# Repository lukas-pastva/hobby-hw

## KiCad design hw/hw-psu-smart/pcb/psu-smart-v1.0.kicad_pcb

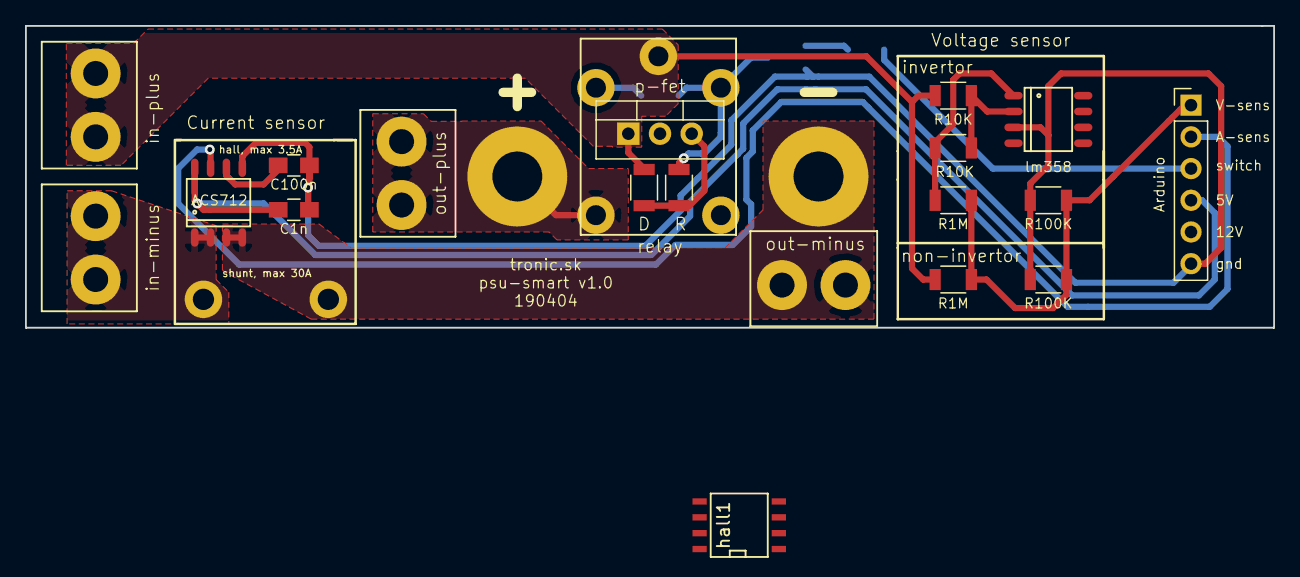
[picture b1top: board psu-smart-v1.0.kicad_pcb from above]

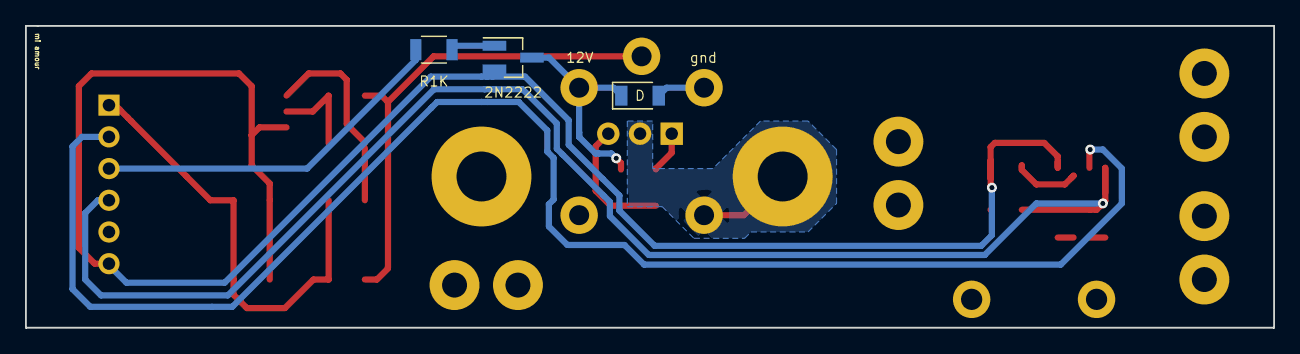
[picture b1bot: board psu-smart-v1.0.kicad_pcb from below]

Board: 2 copper layers, 100.0 x 24.2 mm, 26 parts (3 on the bottom side), 16 nets.

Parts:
ACS712: ACS712; SO-8
C1, C2: C; C_0805_HandSoldering
D1: D; D_1206
D2: D; R_1206
J1: mosfet; TO-220-3_Vertical
J2: shunt; psw-shunt
Q1: Q_PNP_BCE; SOT-23_Handsoldering
R1, R2, R3, R4, R5, R6, R7, R8: R; R_1206
arduino1: arduino; Pin_Header_Straight_1x06_Pitch2.54mm
hall1: hall1; SOIC-8-N
in-minus1: in-minus; psw-konektor-zeleny
in-plus1: in-plus; psw-konektor-zeleny
invertor1: invertor; SO-8
out1: out; psw-bananik
out-gnd1: out-gnd; psw-bananik
out-minus1: out-minus; psw-konektor-zeleny
out-plus1: out-plus; psw-konektor-zeleny
relay1: relay1; psw-relay-small

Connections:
12V: J1.1, R1.2, R2.2, R8.1, in-plus1.1, in-plus1.2, relay1.3
12V-out: J1.2, out1.1, out-plus1.1, out-plus1.2, relay1.5
unnamed: ACS712.6, C2.2
unnamed: D1.1, D2.2, Q1.3, relay1.1
unnamed: D1.2, relay1.2
unnamed: D2.1, J1.3, R8.2
unnamed: Q1.1, R7.2
unnamed: R1.1, R3.2, invertor1.2
unnamed: R3.1, R6.1, invertor1.1
a-sens: ACS712.7, arduino1.2
arduino-5V: ACS712.8, C1.2, arduino1.4
arduino-gnd: ACS712.5, C1.1, C2.1, Q1.2, R4.1, R5.2, arduino1.6, invertor1.3
arduino-relay: R7.1, arduino1.3
in-gnd: ACS712.1, ACS712.2, J2.1, in-minus1.1, in-minus1.2
out-gnd: ACS712.3, ACS712.4, J2.2, out-gnd1.1, out-minus1.1, out-minus1.2
v-sens: R2.1, R4.2, R5.1, R6.2, arduino1.1

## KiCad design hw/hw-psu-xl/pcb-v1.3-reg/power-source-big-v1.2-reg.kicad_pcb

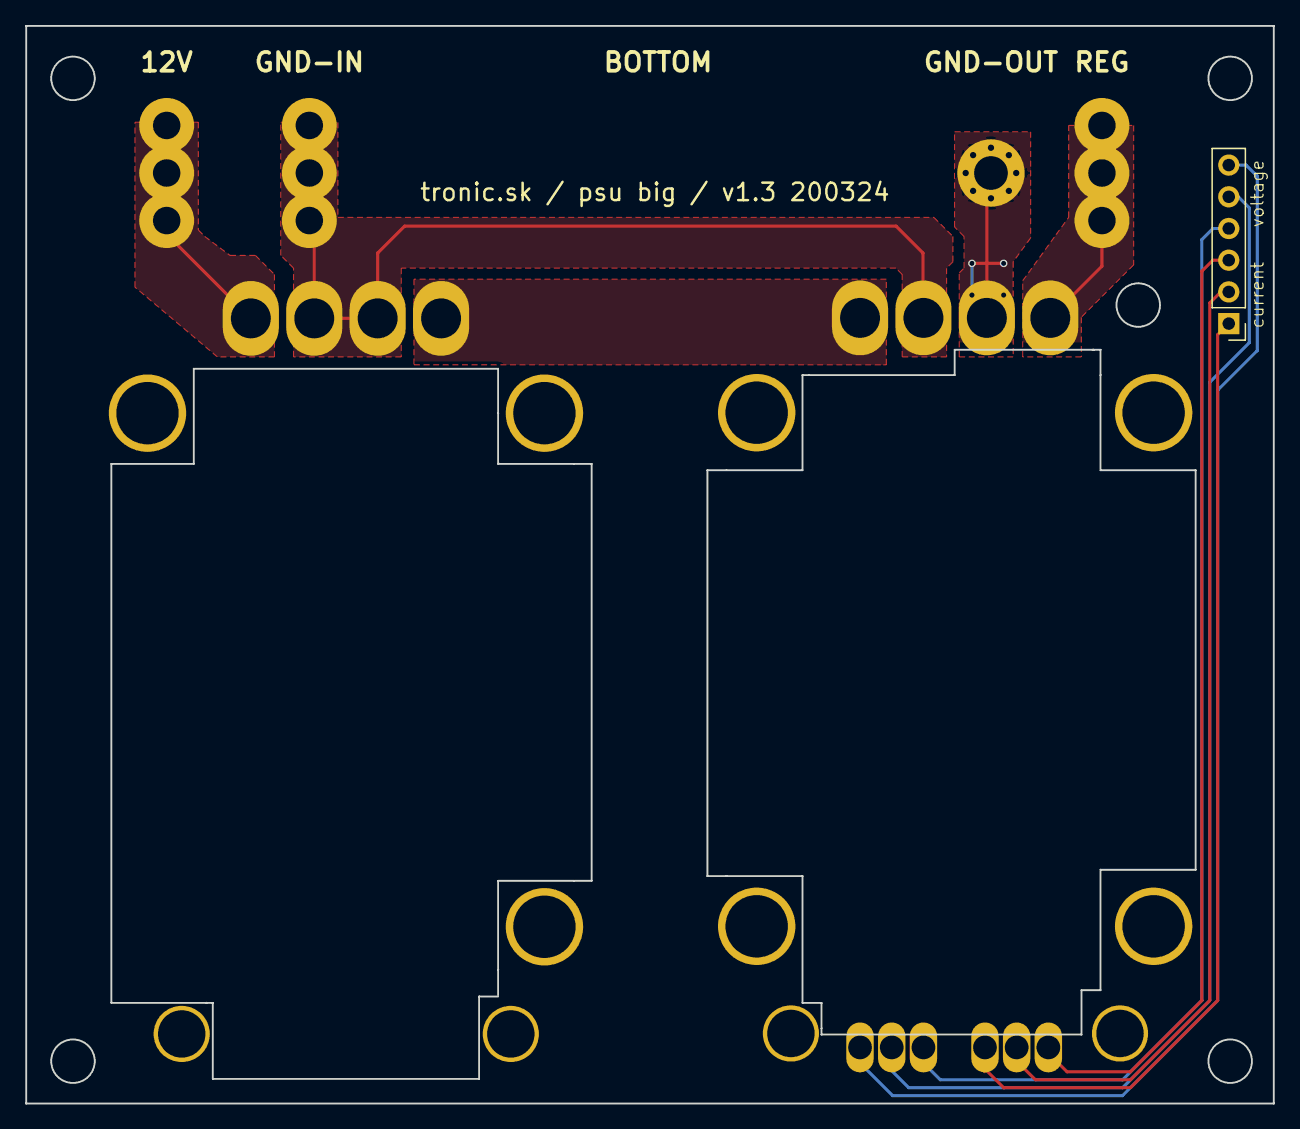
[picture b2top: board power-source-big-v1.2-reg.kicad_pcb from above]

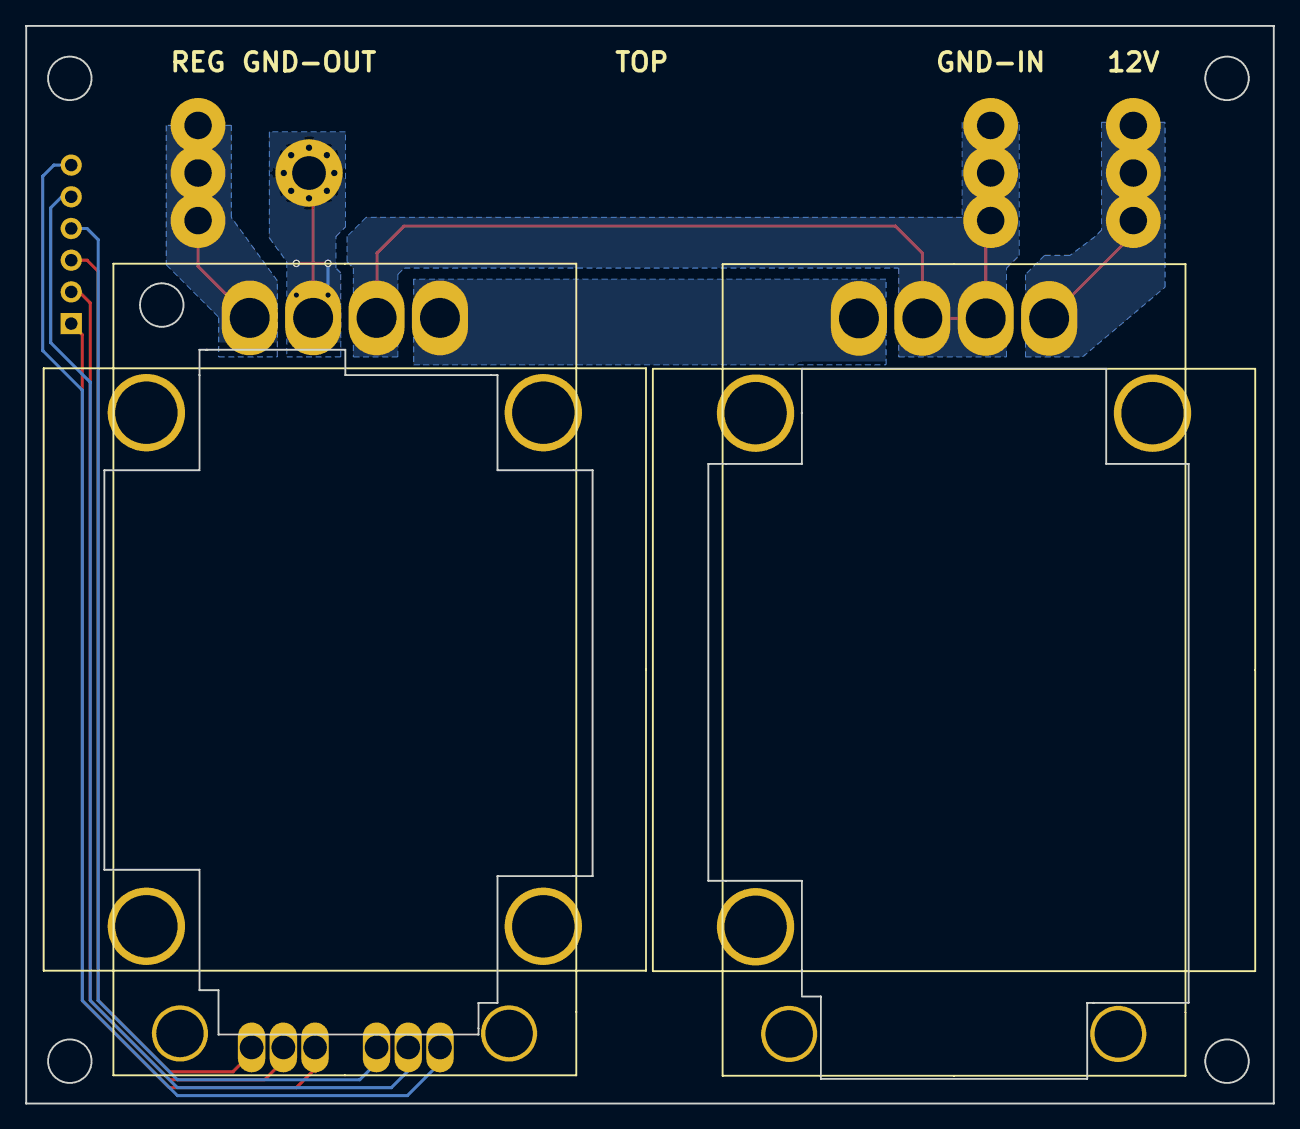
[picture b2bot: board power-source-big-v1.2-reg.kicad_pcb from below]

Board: 2 copper layers, 100.0 x 86.3 mm, 13 parts (2 on the bottom side), 11 nets.

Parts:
12V1, 12V2, 12V3, 12V10, 12V11, 12V12: 12V; MountingHole_2.2mm_M2_Pad
boost1: boost; psw-reg-big-boost
buck1: buck; psw-reg-big-buck
conn-reg-v-a1: conn-reg-v-a; Pin_Header_Straight_1x06_Pitch2.54mm
gnd1, gnd2, gnd3: gnd; MountingHole_2.2mm_M2_Pad
gnd-reg1: gnd-reg; MountingHole_2.7mm_Pad_Via

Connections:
12V: 12V1.1, 12V2.1, 12V3.1, boost1.4
12V-reg: 12V10.1, 12V11.1, 12V12.1, buck1.1
unnamed: boost1.1, buck1.4
gnd: boost1.2, boost1.3, buck1.3, gnd1.1, gnd2.1, gnd3.1
gnd-reg: buck1.2, gnd-reg1.1
reg-a-1: buck1.8, conn-reg-v-a1.4
reg-a-2: buck1.9, conn-reg-v-a1.5
reg-a-3: buck1.10, conn-reg-v-a1.6
reg-v-1: buck1.7, conn-reg-v-a1.1
reg-v-2: buck1.6, conn-reg-v-a1.2
reg-v-3: buck1.5, conn-reg-v-a1.3

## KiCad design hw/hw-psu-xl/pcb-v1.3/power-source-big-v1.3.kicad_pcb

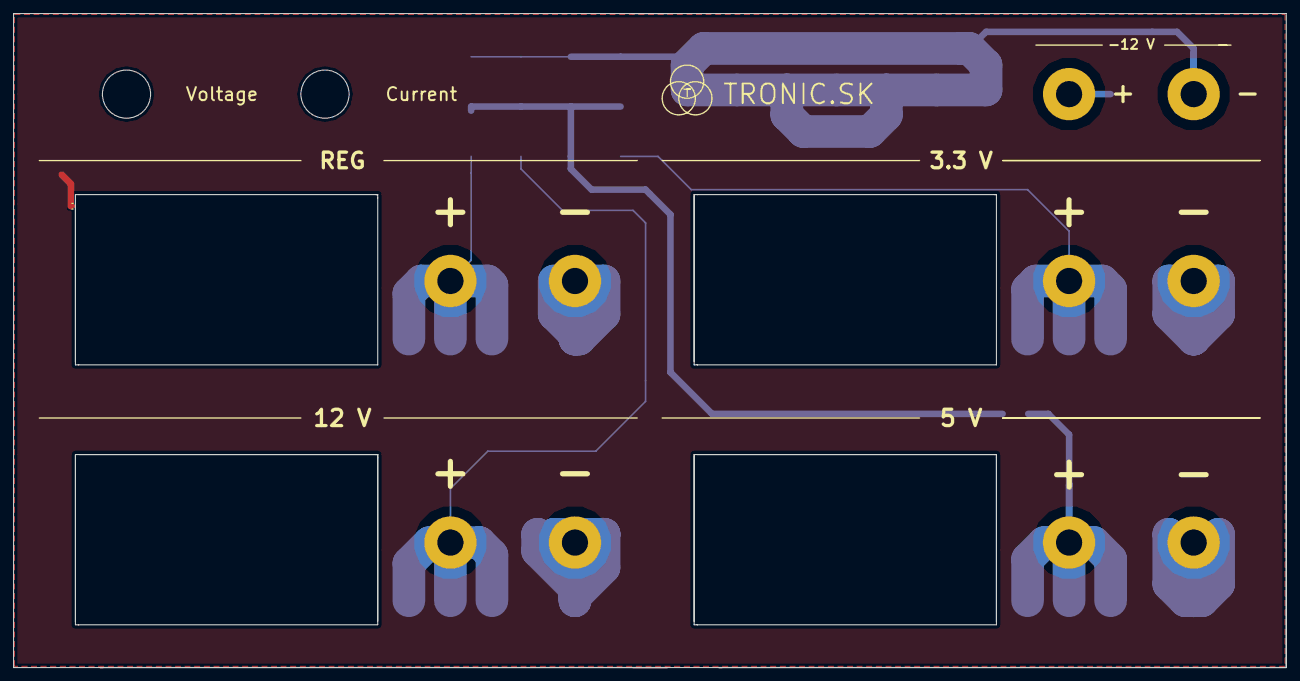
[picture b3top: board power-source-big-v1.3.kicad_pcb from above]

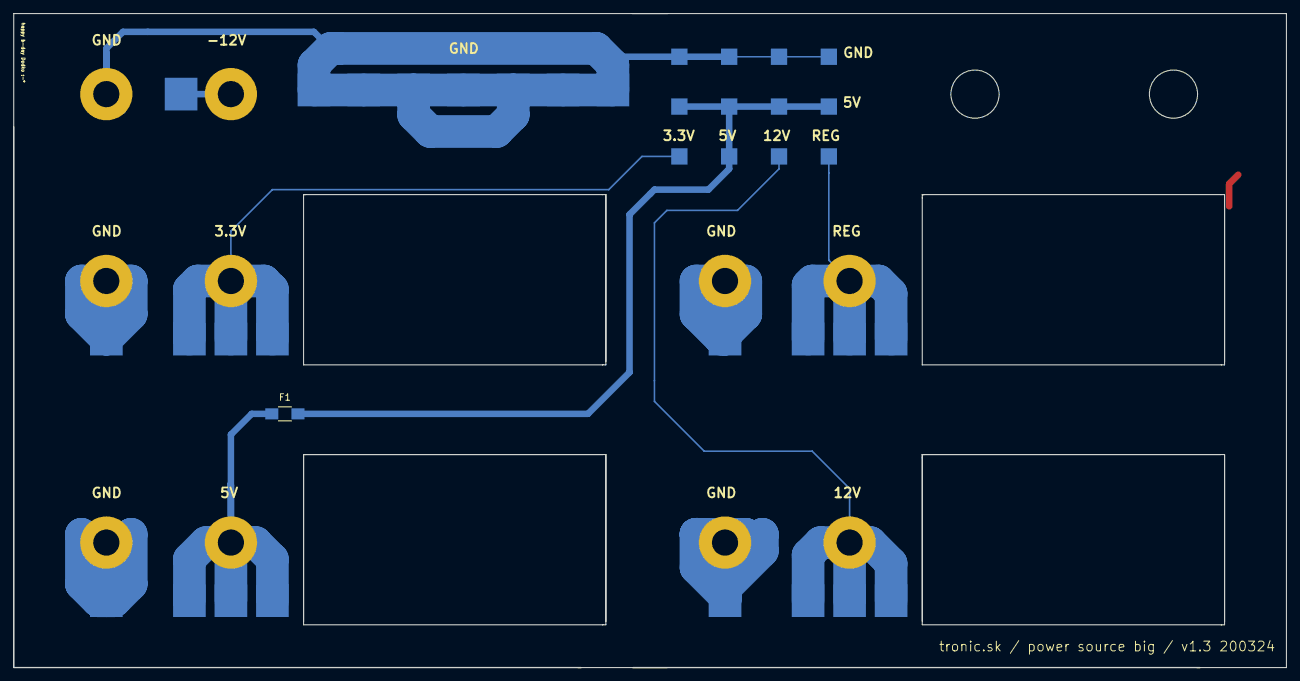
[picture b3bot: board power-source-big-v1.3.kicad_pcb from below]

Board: 2 copper layers, 194.6 x 100.0 mm, 48 parts (47 on the bottom side), 11 nets.

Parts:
3V1, 3V2, 3V3: 3V; psw-kontakt-smd-velky
3V-measure1: 3V-measure; psw-kontakt-smd-maly
5V1, 5V2, 5V3: 5V; psw-kontakt-smd-velky
5V-measure1: 5V-measure; psw-kontakt-smd-maly
5V-meter1, 5V-meter2, 5V-meter3, 5V-meter4: 5V-meter; psw-kontakt-smd-maly
12V1, 12V2, 12V3: 12V; psw-kontakt-smd-velky
12V-measure1: 12V-measure; psw-kontakt-smd-maly
-12V1: -12V; psw-bananik
-12V2: -12V; psw-kontakt-smd-velky
F1: Fuse; R_1206_HandSoldering
GND-3V1, GND-5V1: GND-3V; psw-bananik
GND-3V2: GND-3V; psw-kontakt-smd-velky
GND-5V2: GND-5V; psw-kontakt-smd-velky
GND-12V1, GND-12V3: GND-12V; psw-bananik
GND-12V2: GND-12V; psw-kontakt-smd-velky
GND-REG1: GND-REG; psw-bananik
GND-REG2: GND-REG; psw-kontakt-smd-velky
R1: R; R_0201
REG1, REG2, REG3: REG; psw-kontakt-smd-velky
REG-measure1: REG-measure; psw-kontakt-smd-maly
gnd1, gnd2, gnd3, gnd4, gnd5, gnd6, gnd7: gnd; psw-kontakt-smd-velky
gnd-meter1, gnd-meter2, gnd-meter3, gnd-meter4: gnd-meter; psw-kontakt-smd-maly
panel-3V1: panel-3V; psw-bananik
panel-5V1: panel-5V; psw-bananik
panel-12V1: panel-12V; psw-bananik
panel-REG1: panel-REG; psw-bananik

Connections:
3V: 3V1.1, 3V2.1, 3V3.1, 3V-measure1.1, panel-3V1.1
5V: 5V1.1, 5V2.1, 5V3.1, 5V-measure1.1, 5V-meter1.1, 5V-meter2.1, 5V-meter3.1, 5V-meter4.1, F1.1, F1.2, panel-5V1.1
12V: 12V1.1, 12V2.1, 12V3.1, 12V-measure1.1, panel-12V1.1
-12V: -12V1.1, -12V2.1
GND: GND-12V3.1, gnd1.1, gnd2.1, gnd3.1, gnd4.1, gnd5.1, gnd6.1, gnd7.1, gnd-meter1.1, gnd-meter2.1, gnd-meter3.1, gnd-meter4.1
GND-3V: GND-3V1.1, GND-3V2.1
GND-5V: GND-5V1.1, GND-5V2.1
GND-12V: GND-12V1.1, GND-12V2.1
GND-REG: GND-REG1.1, GND-REG2.1
REG: REG1.1, REG2.1, REG3.1, REG-measure1.1, panel-REG1.1
aaa: R1.1, R1.2

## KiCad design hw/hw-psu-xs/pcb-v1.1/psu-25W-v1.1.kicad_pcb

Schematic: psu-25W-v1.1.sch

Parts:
12V1: 12V; MountingHole_2.5mm_Pad_Via
GND1: GND; MountingHole_2.5mm_Pad_Via
J1: USB_A; psw-usb-a-vertical
J3: zem; psw-kontakt-smd-velky
J9, J10: pot-1; psw-pot-through-horizontal
J12, J13, J14, J15: srobik; psw-srobik-3.5mm
R1, R2, R3, R4: R; R_1206
fan1: fan; Pin_Header_Straight_1x03_Pitch2.54mm
minus1: minus; psw-bananik
plus1: plus; psw-bananik
reg1: reg; psw-reg-small-buck-boost
reg-usb1: reg-usb; psw-dc-dc-lm2596-HOLE
va1: va; psw-va-meter

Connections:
5V: J1.4 (GND), R4.2, reg-usb1.3
12V: 12V1.1, R3.2, reg1.4, reg-usb1.1, va1.1
12v-reg: plus1.1, reg1.1, va1.3
unnamed: R3.1, R4.1, fan1.1, fan1.2
gnd: GND1.1, J1.1 (VBUS), J1.5 (Shield), fan1.3, reg1.2, reg1.3, reg-usb1.2, reg-usb1.4, va1.2, va1.4
gnd-out: va1.5; also elsewhere on the board
reg-i-1: J10.3, R2.2, reg1.5
reg-i-2: J10.2, reg1.6
reg-i-3: J10.1, R2.1, reg1.7
reg-u-1: J9.3, R1.1, reg1.8
reg-u-2: J9.2, reg1.9
reg-u-3: J9.1, R1.2, reg1.10
zem: J3.1, J12.1, J13.1, J14.1, J15.1

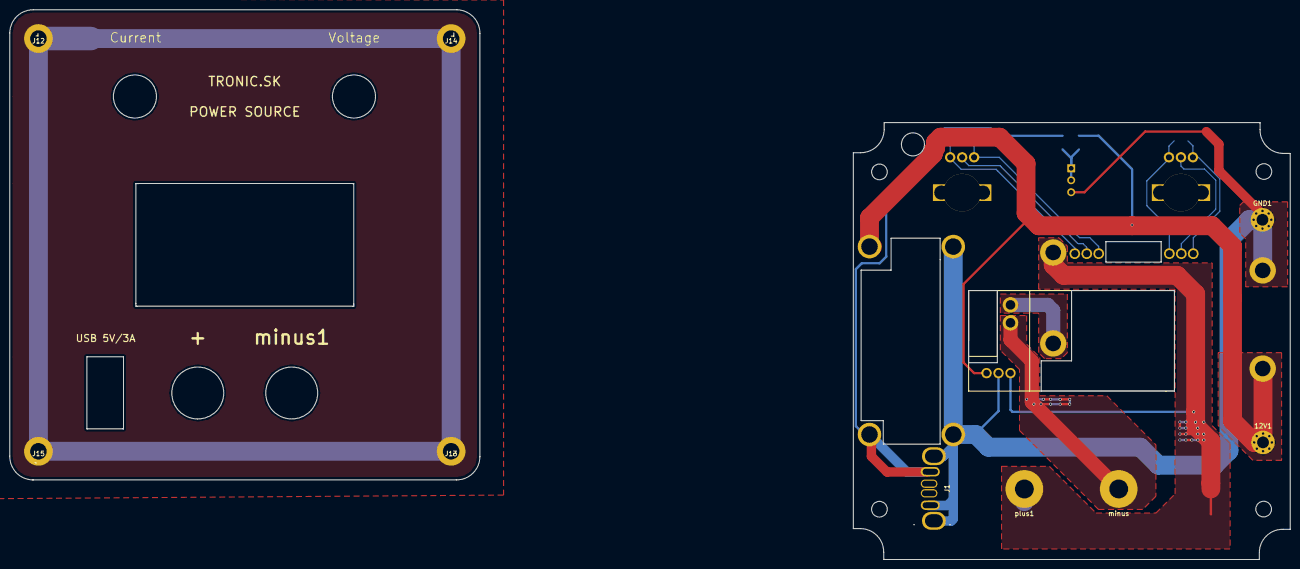
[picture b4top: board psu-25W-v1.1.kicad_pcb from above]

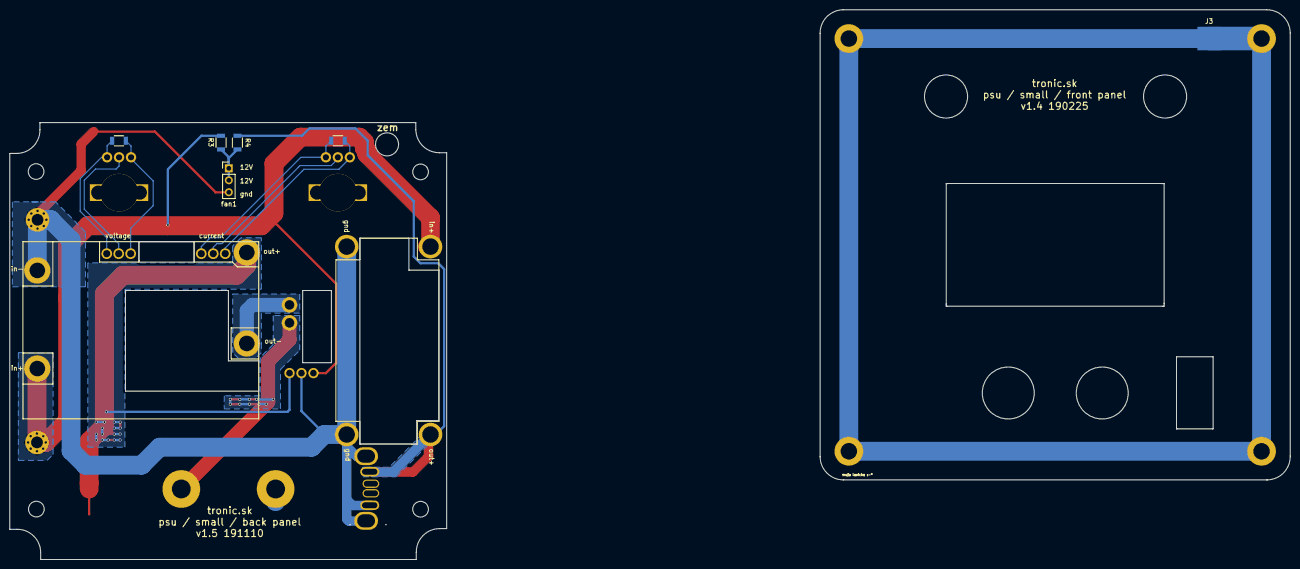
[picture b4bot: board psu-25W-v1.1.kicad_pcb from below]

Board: 2 copper layers, 271.7 x 116.6 mm, 21 parts (8 on the bottom side), 13 nets.

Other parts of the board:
minus: minus; psw-bananik

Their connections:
gnd-out: minus.1; also elsewhere on the board

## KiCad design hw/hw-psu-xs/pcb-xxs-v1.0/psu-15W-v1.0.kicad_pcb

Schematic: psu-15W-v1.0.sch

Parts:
12V1: 12V; MountingHole_3.2mm_M3_Pad_Via
GND1: GND; MountingHole_3.2mm_M3_Pad_Via
J1: v-meter; psw-v-meter
J2: Conn_01x06; psw-dc-dc-lm2596-pot
J3: zem; psw-kontakt-smd-velky
J9: pot-1; psw-pot-through-horizontal
J12, J13, J14, J15: srobik; psw-srobik-3.5mm
R1: R; R_1206
minus1: minus; psw-bananik
plus1, plus2: plus; psw-bananik
reg-boost1: reg-boost; psw-dc-dc-lm2596-HOLE

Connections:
12V: 12V1.1, J1.1, reg-boost1.1
12v-reg: J1.3, J2.3, plus1.1
35V: J2.1, reg-boost1.3
gnd: GND1.1, J1.2, J2.2, plus2.1, reg-boost1.2, reg-boost1.4
reg-u-1: J2.4, J9.3, R1.1
reg-u-2: J2.5, J9.2
reg-u-3: J2.6, J9.1, R1.2
zem: J3.1, J12.1, J13.1, J14.1, J15.1

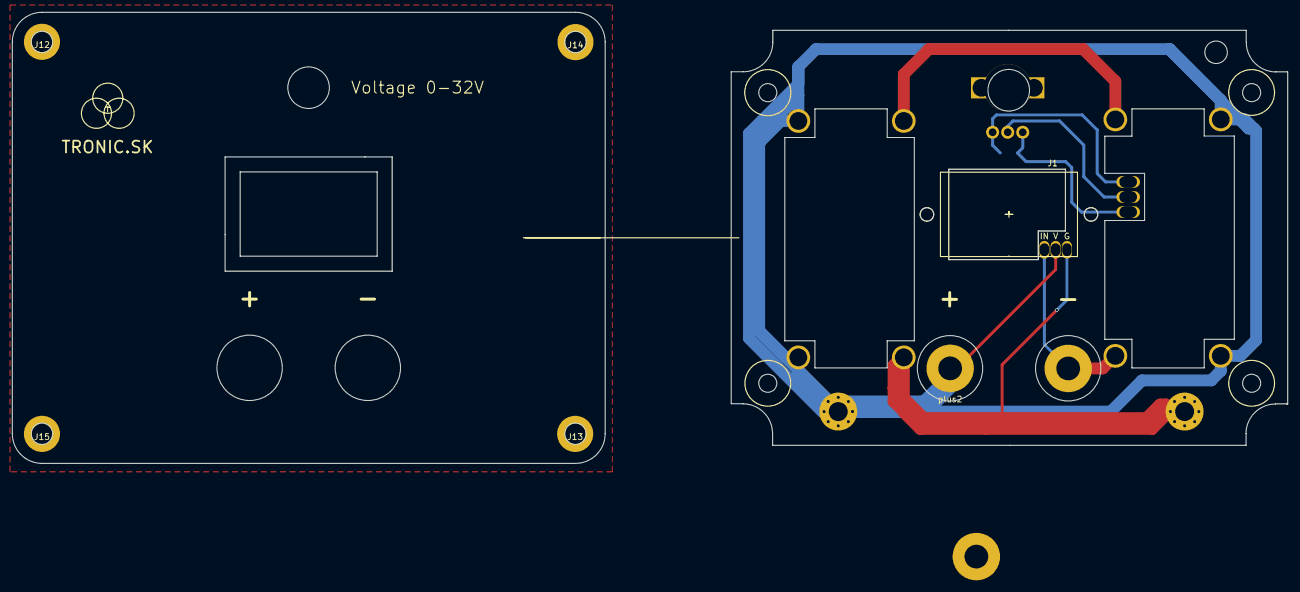
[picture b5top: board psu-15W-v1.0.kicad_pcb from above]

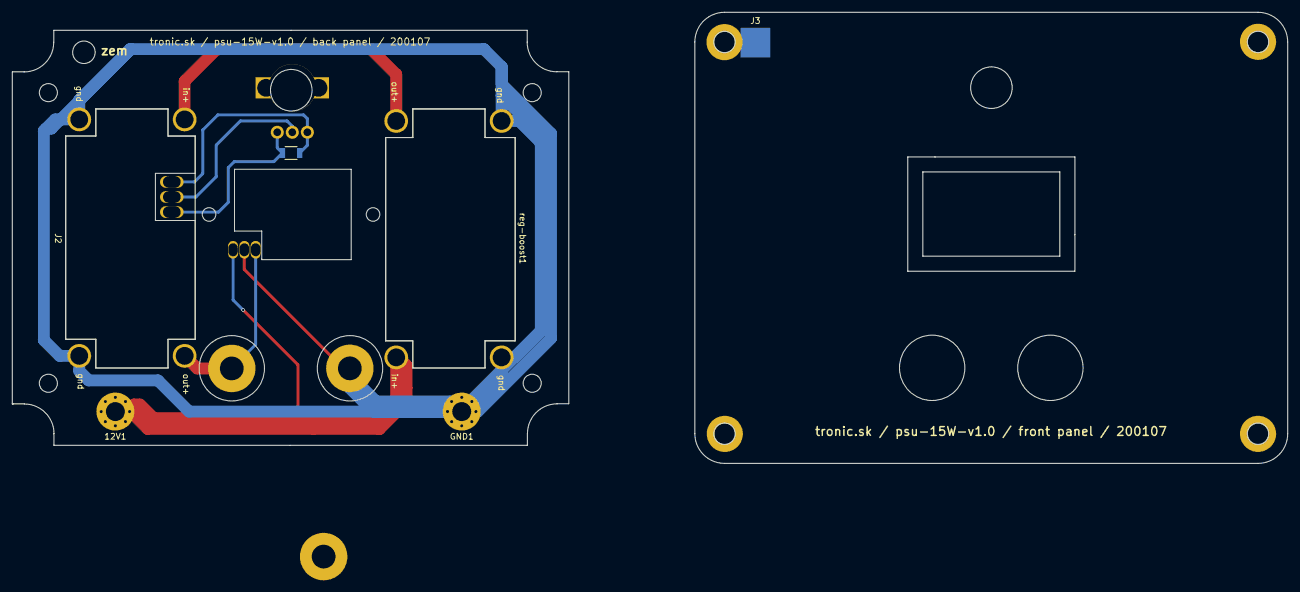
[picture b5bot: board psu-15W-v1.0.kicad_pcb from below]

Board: 2 copper layers, 215.1 x 76.1 mm, 17 parts (6 on the bottom side), 8 nets.

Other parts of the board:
-: minus; psw-bananik
-#2: minus; psw-bananik
minus: minus; psw-bananik

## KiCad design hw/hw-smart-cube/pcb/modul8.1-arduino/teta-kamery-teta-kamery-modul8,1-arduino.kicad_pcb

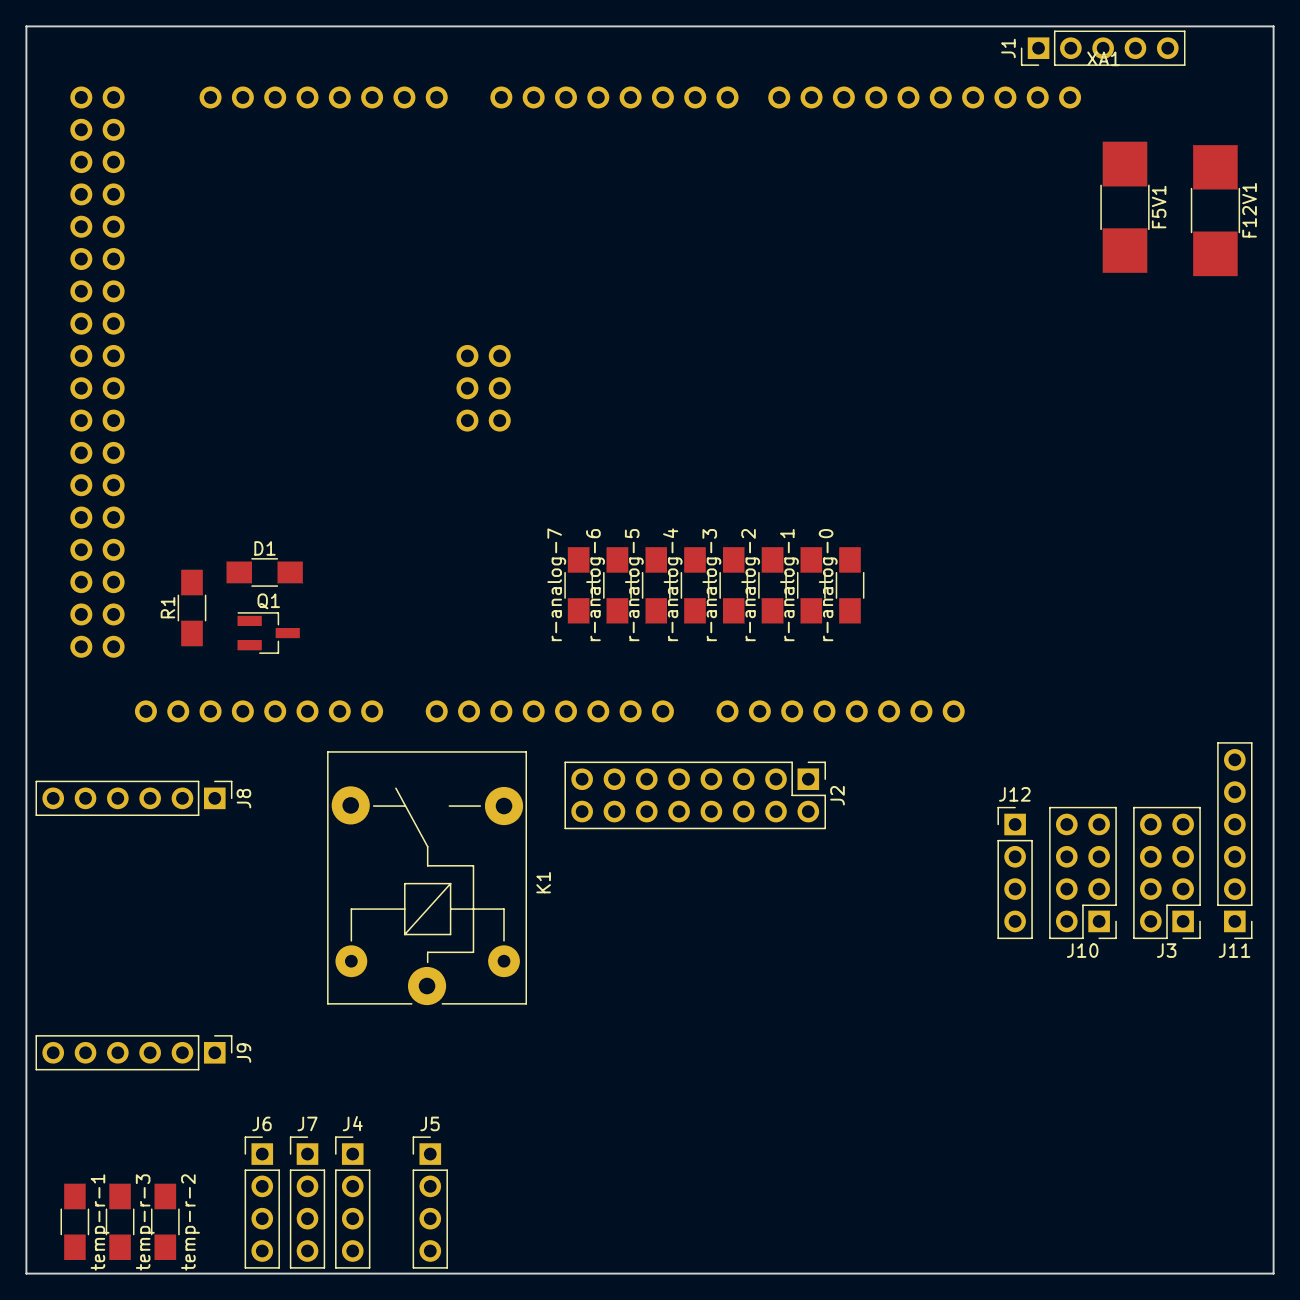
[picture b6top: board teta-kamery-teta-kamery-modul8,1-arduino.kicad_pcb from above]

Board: 2 copper layers, 98.0 x 98.0 mm, 30 parts (0 on the bottom side), 45 nets, no tracks yet.

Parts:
D1: D; R_1206_HandSoldering
F5V1, F12V1: R; R_1812_HandSoldering
J1: i2c; Pin_Header_Straight_1x05_Pitch2.54mm
J2: analog-sensors-1; Pin_Header_Straight_2x08_Pitch2.54mm
J3: Serial; Pin_Header_Straight_2x04_Pitch2.54mm
J4, J6, J7: temp1; Pin_Header_Straight_1x04_Pitch2.54mm
J5: display; Pin_Header_Straight_1x04_Pitch2.54mm
J8: eth-1; Pin_Header_Straight_1x06_Pitch2.54mm
J9: eth-2; Pin_Header_Straight_1x06_Pitch2.54mm
J10: digital; Pin_Header_Straight_2x04_Pitch2.54mm
J11: Conn_01x06; Pin_Header_Straight_1x06_Pitch2.54mm
J12: 433; Pin_Header_Straight_1x04_Pitch2.54mm
K1: SANYOU_SRD_Form_C; Relay_SPDT_SANYOU_SRD_Series_Form_C
Q1: Q_NPN_BCE; SOT-23_Handsoldering
R1: R; R_1206_HandSoldering
XA1: Arduino_Mega2560_Shield; Arduino_Mega2560_Shield-psw-mirror
r-analog-0, r-analog-1, r-analog-2, r-analog-3, r-analog-4, r-analog-5, r-analog-6, r-analog-7: R; R_1206_HandSoldering
temp-r-1, temp-r-2, temp-r-3: R; R_1206_HandSoldering

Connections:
3v: J9.2, J9.3, XA1.3V3
5v: F5V1.2, J4.1, J5.2, J6.1, J7.1, J11.4, J12.1, r-analog-0.1, r-analog-1.1, r-analog-2.1, r-analog-3.1, r-analog-4.1, r-analog-5.1, r-analog-6.1, r-analog-7.1, temp-r-1.2, temp-r-2.2, temp-r-3.2
5v-input: F5V1.1, J1.1
12v: D1.1, F12V1.2, J11.5, K1.1, K1.5
12v-arduino: K1.4, XA1.VIN
12v-input: F12V1.1, J1.2
unnamed: D1.2, K1.2, Q1.3
unnamed: Q1.1, R1.1
a0: J2.1, XA1.A0, r-analog-0.2
a1: J2.3, XA1.A1, r-analog-1.2
a2: J2.5, XA1.A2, r-analog-2.2
a3: J2.7, XA1.A3, r-analog-3.2
a4: J2.9, XA1.A4, r-analog-4.2
a5: J2.11, XA1.A5, r-analog-5.2
a6: J2.13, XA1.A6, r-analog-6.2
a7: J2.15, XA1.A7, r-analog-7.2
clk: J8.4, XA1.SCK
d0: J3.7, XA1.D0
d1: J3.8, XA1.D1
d2: J6.2, XA1.D2, temp-r-1.1
d3: J12.2, J12.3, XA1.D3
d4: J4.2, XA1.D4, temp-r-2.1
d5: J10.1, XA1.D5
d6: J10.2, XA1.D6
d7: J10.3, XA1.D7
d8: J10.4, XA1.D8
d9: J10.8, XA1.D9
d10: J8.5, XA1.D10
d11: J10.7, XA1.D11
d12: J10.6, XA1.D12
d13: J10.5, XA1.D13
d14: J3.5, XA1.D14
d15: J3.6, XA1.D15
d16: J3.3, XA1.D16
d17: J3.4, XA1.D17
d18: J3.1, XA1.D18
d19: J3.2, XA1.D19
d22: J7.2, XA1.D22, temp-r-3.1
d23: R1.2, XA1.D23
gnd: J1.3, J2.2, J2.4, J2.6, J2.8, J2.10, J2.12, J2.14, J2.16, J4.4, J5.1, J6.4, J7.4, J8.1, J8.2, J9.1, J11.6, J12.4, Q1.2, XA1.GND1, XA1.GND2, XA1.GND3, XA1.GND5, XA1.GND6
rst: J9.5, J11.3, XA1.RST1
scl: J1.5, J5.4, J11.1, XA1.SCL
sda: J1.4, J5.3, J11.2, XA1.SDA
si: J8.3, XA1.MOSI
so: J9.6, XA1.MISO
